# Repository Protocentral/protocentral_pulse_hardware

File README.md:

# ProtoCentral Pulse — Hardware

Open-source hardware design files for the **ProtoCentral Pulse** pulse-oximetry / heart-rate breakout — built around the [Maxim MAX30102](https://www.analog.com/en/products/max30102.html) integrated pulse-oximeter and heart-rate sensor, which combines the red and IR LEDs, photodiode, and analog front end in a single OLGA-14 package.

The board streams raw PPG (photoplethysmogram) samples over I²C; SpO₂ and heart-rate calculation runs on your host MCU using our open-source Arduino library. That keeps the full optical signal visible, which is what makes the board useful for research, algorithm development, and teaching.

## Links

| | |
|---|---|
| 🛒 Product page | https://protocentral.com/product/pulse-3-pulse-ox-heart-rate-sensor-based-on-max30102-qwiic-compatible/ |
| 💻 Arduino library | https://github.com/Protocentral/protocentral_max30102_arduino |
| 📄 IC datasheet (Analog Devices / Maxim) | https://www.analog.com/media/en/technical-documentation/data-sheets/MAX30102.pdf |

## Specifications

- **Sensor:** Maxim MAX30102 — integrated red (660 nm) + IR (880 nm) LEDs, photodiode, and AFE
- **Output:** raw 18-bit PPG samples per channel, read over the sensor FIFO
- **Interface:** I²C, fixed address `0x57`
- **Connector:** Qwiic (1 mm 4-pin, right-angle)
- **Supply:** onboard AP2112K-1.8 V LDO with level translation to the host
- **Board:** 29.7 × 16.4 mm, 6-layer

## Revisions

| Revision | Design files | Notes |
|---|---|---|
| **v4** (current) | [`hardware/`](hardware/) | KiCad 10; 6-layer; Qwiic |
| v3 and earlier | [`Pulse_MAX30102/Hardware/`](https://github.com/Protocentral/Pulse_MAX30102/tree/master/Hardware) | Eagle; retained in the original repository so existing links keep working |

## Repository layout

| Folder | Contents |
|---|---|
| [`hardware/`](hardware/) | KiCad project (schematic + PCB layout) and the exported [schematic PDF](hardware/protocentral-pulse-v4-schematic.pdf) |

## Important notice

This device is intended for research, education, and evaluation use only. It is **not** a medical diagnostic instrument and is not FDA, CE, or FCC approved for consumer use.

## License

The hardware design files in this repository are licensed under the **CERN Open Hardware Licence Version 2 – Permissive (CERN-OHL-P v2)**. See [LICENSE](LICENSE).

The accompanying firmware/library (in the separate [protocentral_max30102_arduino](https://github.com/Protocentral/protocentral_max30102_arduino) repository) is licensed under the MIT License.

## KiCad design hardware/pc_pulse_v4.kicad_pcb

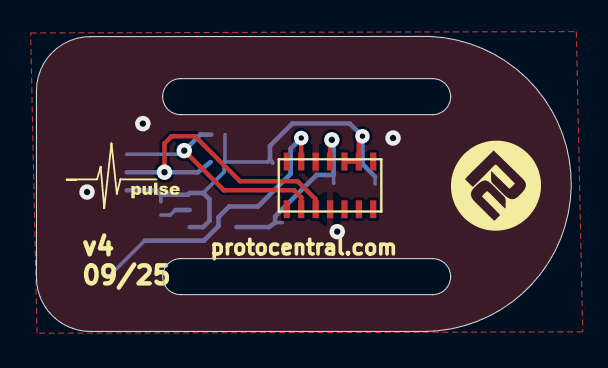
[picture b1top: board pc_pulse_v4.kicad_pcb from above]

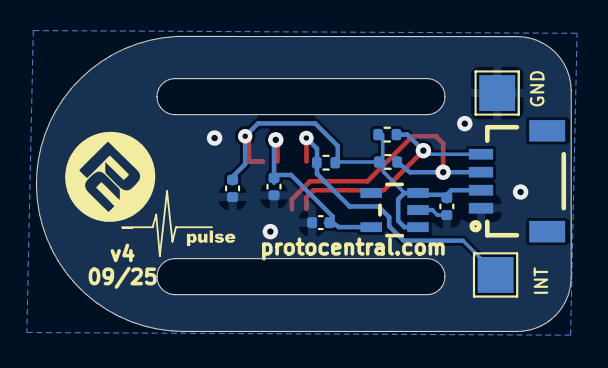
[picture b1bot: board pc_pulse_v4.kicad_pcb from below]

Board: 6 copper layers, 29.7 x 16.4 mm, 12 parts (11 on the bottom side), 6 nets.

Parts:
C1: 1uF; C_0402_1005Metric
C2: 10uF; C_0402_1005Metric
C25, C26: 1u; C_0402_1005Metric
J1: Qwiic1; 1X04_1MM_RA
R9, R10, R11: 10k; R_0402_1005Metric
TP1, TP3: TestPoint; TestPoint_Pad_2.0x2.0mm
U1: AP2112K-1.8V; SOT23-5
U$1: MAX30100; OESIP-14

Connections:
1.8V: C1.1, C26.2, U1.5 (OUT), U$1.11 (VDD)
+3V3: C2.1, C25.2, J1.2, R9.2, R10.2, R11.2, U1.1 (IN), U1.3 (EN), U$1.9 (R_LED+), U$1.10 (IR_LED+)
/SCL_OUT: J1.4, R10.1, U$1.2 (SCL)
/SDA_OUT: J1.3, R9.1, U$1.3 (SDA)
GND: C1.2, C2.2, C25.1, C26.1, J1.1, TP1.1, U1.2 (GND), U$1.4 (PGND), U$1.12 (GND)
INT_OUT: R11.1, TP3.1, U$1.13 (~INT)
